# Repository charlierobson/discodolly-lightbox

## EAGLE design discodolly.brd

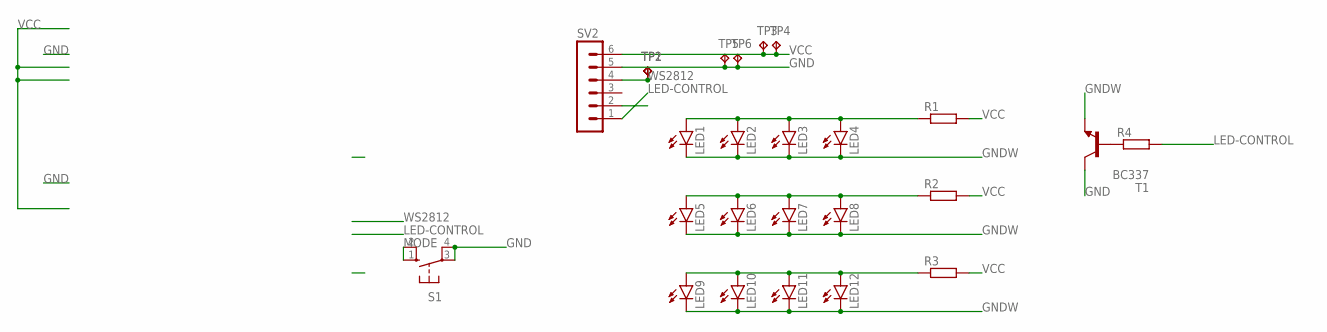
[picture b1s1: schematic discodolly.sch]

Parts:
LED1, LED2, LED3, LED4, LED5, LED6, LED7, LED8, LED9, LED10, LED11, LED12: LEDCHIPLED_1206; CHIPLED_1206
R1, R2, R3, R4: R-EU_M1206; M1206
S1: 10-XX; B3F-10XX
SV2: MA06-1
T1: BC337; TO92
TP1, TP2, TP3, TP4, TP5, TP6: TPTP20SQ; TP20SQ

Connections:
GND: S1.3, S1.4 (P1), SV2.5, T1.3 (C), TP5.TP, TP6.TP
GNDW: LED1.C, LED2.C, LED3.C, LED4.C, LED5.C, LED6.C, LED7.C, LED8.C, LED9.C, LED10.C, LED11.C, LED12.C, T1.1 (E)
LED-CONTROL: R4.2, SV2.1
MODE: S1.1 (S), S1.2 (S1), SV2.2
unnamed: LED1.A, LED2.A, LED3.A, LED4.A, R1.1
unnamed: LED5.A, LED6.A, LED7.A, LED8.A, R2.1
unnamed: LED9.A, LED10.A, LED11.A, LED12.A, R3.1
unnamed: R4.1, T1.2 (B)
VCC: R1.2, R2.2, R3.2, SV2.6, TP3.TP, TP4.TP
WS2812: SV2.4, TP1.TP, TP2.TP

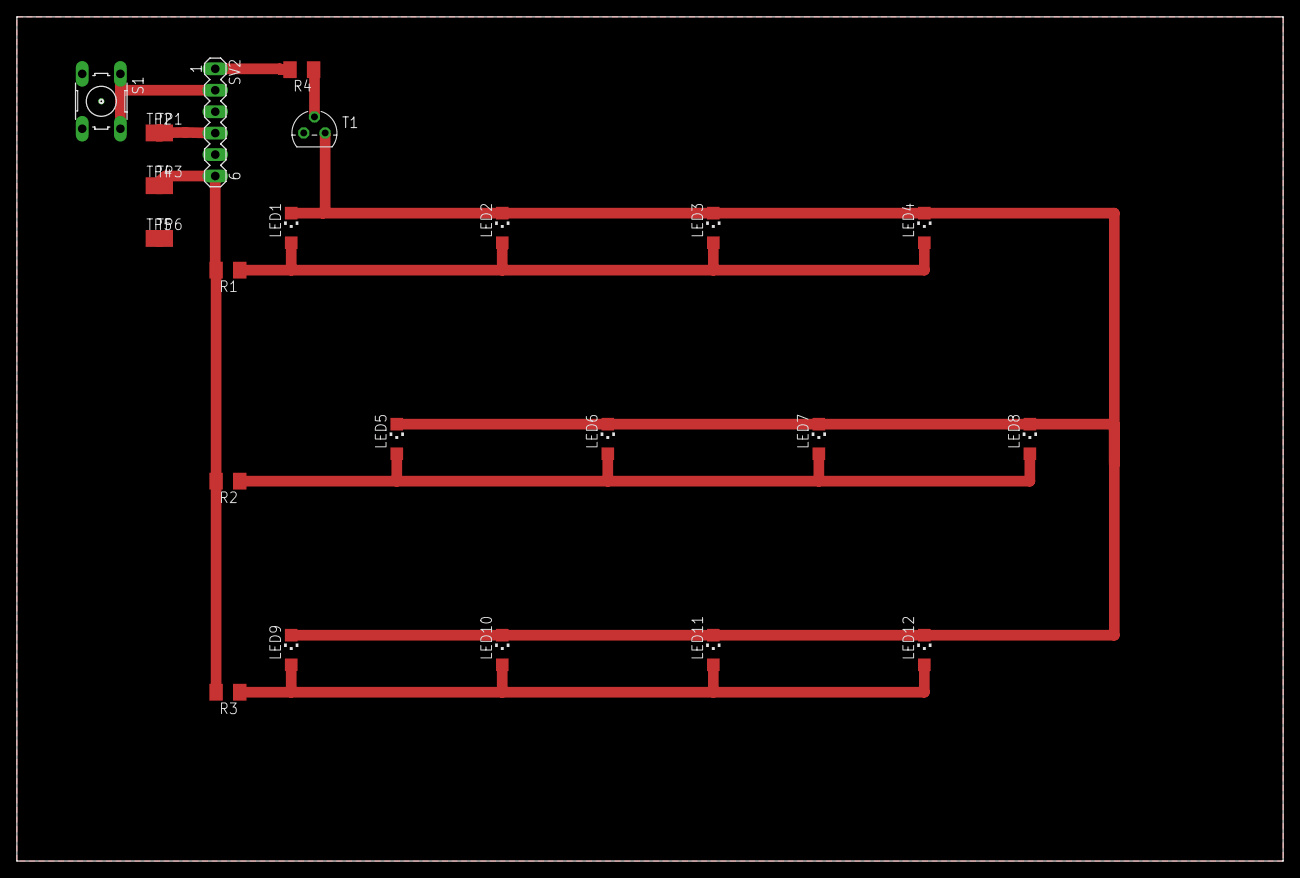
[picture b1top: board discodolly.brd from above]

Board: 2 copper layers, 150.0 x 100.0 mm, 25 parts (0 on the bottom side), 10 nets.

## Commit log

2019-05-21 board
2019-05-21 remove lock files
2019-05-21 adding arduino sketch
2019-05-22 luring disco dollies
2019-05-22 add sleep mode
2019-05-22 approve overlaps
